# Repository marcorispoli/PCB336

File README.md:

NOTE DI DEBUG

17/04/2026

- Manca in Lista Parti L1.
 Aggiunto manualmente

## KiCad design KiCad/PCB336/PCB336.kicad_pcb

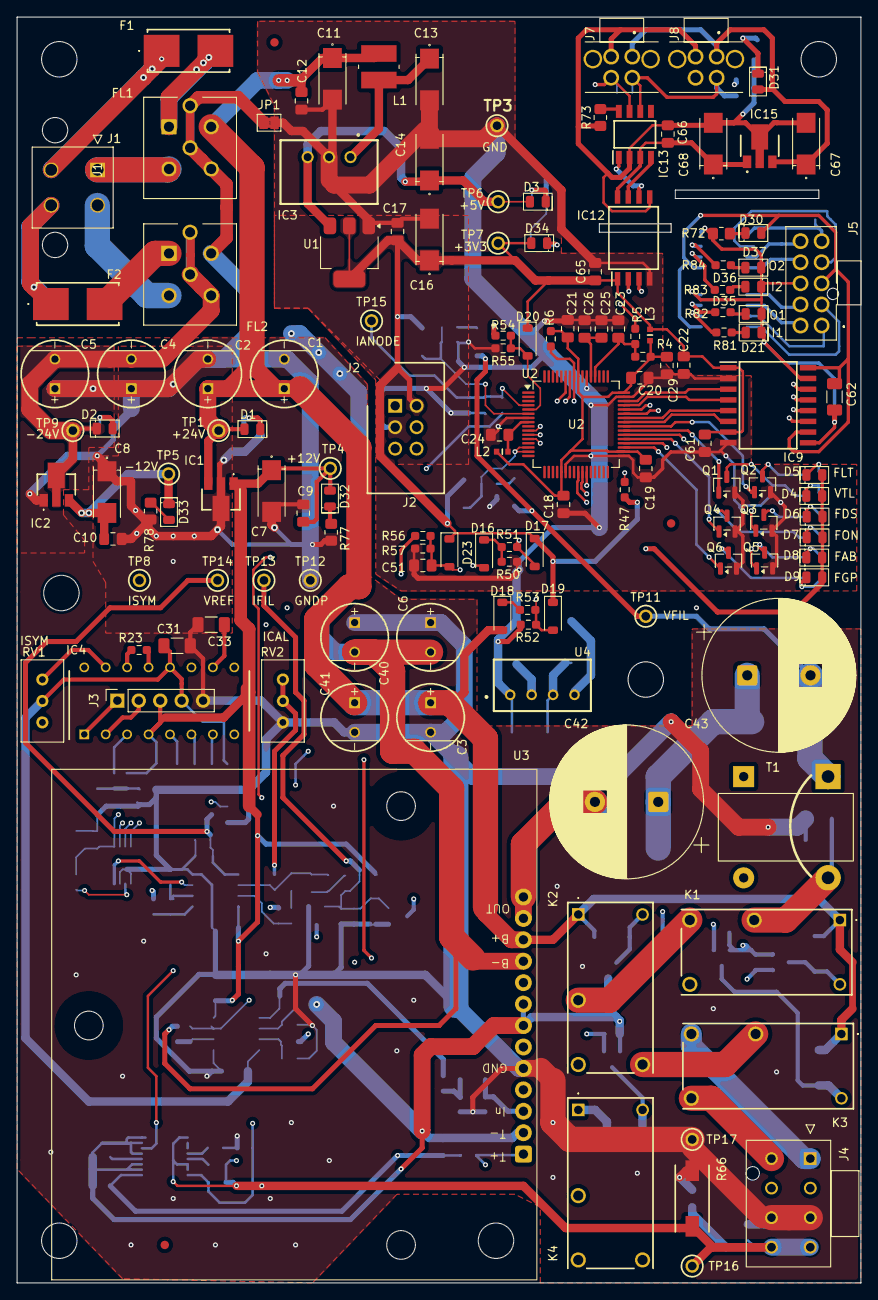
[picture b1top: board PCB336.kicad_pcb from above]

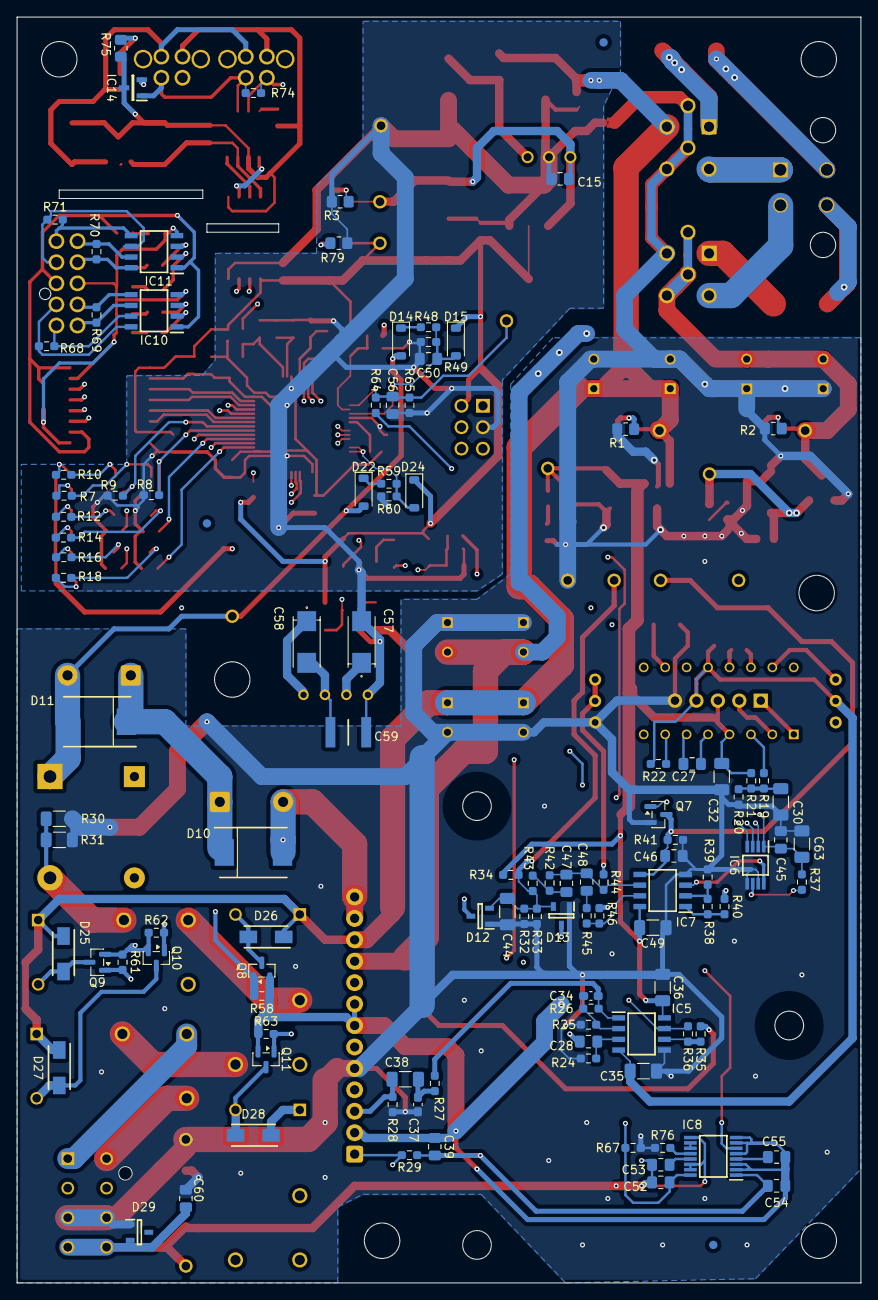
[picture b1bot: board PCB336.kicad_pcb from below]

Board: 4 copper layers, 100.0 x 150.0 mm, 250 parts (110 on the bottom side), 150 nets.

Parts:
C1, C2, C3, C4, C5, C6, C40, C41: 33uF; WCAP-HTG5_D8_H9_P3.5
C7, C8, C11, C13, C14, C16, C57, C58, C67, C68: 4.7uF; T491C
C9, C10, C12, C15, C17, C18, C19, C20, C21, C22, C23, C24, C25, C28, C39, C45, C46, C47, C50, C51, C52, C53, C54, C55, C60, C61, C65, C66: 100nF; C_0805_2012Metric_Pad1.18x1.45mm_HandSolder
C26: 4u7; C_0805_2012Metric_Pad1.18x1.45mm_HandSolder
C27, C56: 10nF; C_0805_2012Metric_Pad1.18x1.45mm_HandSolder
C29: 10uF; C_0805_2012Metric_Pad1.18x1.45mm_HandSolder
C30, C44: 10uF; C_1206_3216Metric_Pad1.33x1.80mm_HandSolder
C31, C32, C33, C35, C36, C38, C49, C62, C63: 1uF; C_1206_3216Metric_Pad1.33x1.80mm_HandSolder
C34: 100pF; C_0603_1608Metric_Pad1.08x0.95mm_HandSolder
C37: 470pF; C_0603_1608Metric_Pad1.08x0.95mm_HandSolder
C42, C43: 100uF; CP_Radial_D18.0mm_P7.50mm
C48: 47nF; C_0805_2012Metric_Pad1.18x1.45mm_HandSolder
C59: 470pF; C470pF_WURTH_APC4632X160N
D1, D2, D3, D30, D31, D32, D33, D34: GREEN; LED_0805
D4: BLUE; LED_0805
D5: RED; LED_0805
D6, D7, D8, D9, D21, D35, D36, D37: YELLOW; LED_0805
D10, D11: SK56C
D12, D13: BAT754S,215
D14, D15, D16, D17, D18, D19, D20, D22, D23, D24: 1N4148W; D_SOD-123
D25, D26, D27, D28: ES1A
D29: MMBZ6V2AL,215
F1, F2: 0154003.DRT; Littlefuse_serie_0154
FL1, FL2: BNX012-01; BNX01201
IC1: NJM78L12UA-TE1; NJM78L12UATE1
IC2: NJM79L12SU3-TE1
IC3: TSR_0.5-2450; TSR-0.5-2433
IC4: XR2206CP-F; XR2206CP
IC5: LM1458MX_NOPB; SOIC_LM1458M
IC6: MCP4821-E/MS; MCP4821_EMS
IC7: LM358BAIDR
IC8: ADUM3195BRQZ; SOP64P599X175-16N
IC9: ISO6742FDWR; ISO6742FDWR_SOIC
IC10, IC11: ADM4857ARZ-REEL7; ADM4857_SOIC
IC12: MAX22246CAWA_V+; MAX22246_SOIC127P1031X265-8N
IC13: TJA1050T_CM,118; TJA1050T_SOIC127P600X175-8N
IC14: ESD2CAN24DBZRQ1
IC15: NJM78L05UA-TE1
J1: 39-29-9043; 39-29-904Y
J2: 61200621621; uCProg_61200621621
J3: Piazzolato; PinSocket_1x05_P2.54mm_Vertical
J4: MOLEX_172298-1108; MOLEX_172298_1108
J5: 105310-2210; 1053102210
J7, J8: 105312-1104; NANOFIT_1053121104
JP1: SolderJumper_2_Bridged; SolderJumper-2_P1.3mm_Bridged2Bar_Pad1.0x1.5mm
K1, K2, K3, K4: 32.21.7.024.4000; 322170244000
L1: SRR4828A-8R2Y; SRR4828A120M
L2, L3: BLM18BD102SN1D; BLM18SP221SN1B
Q1, Q2, Q3, Q4, Q5, Q6, Q7, Q8, Q9, Q10, Q11: 2N7002LT1G; SOT-23
R1, R2, R75: 4K7; R_0805_2012Metric_Pad1.20x1.40mm_HandSolder
R3: 870R; R_0805_2012Metric_Pad1.20x1.40mm_HandSolder
R4, R24, R36, R37, R38, R39, R42, R43, R48, R51, R52, R56, R59, R67: 10K; R_0603_1608Metric_Pad0.98x0.95mm_HandSolder
R5: 330R; R_0603_1608Metric_Pad0.98x0.95mm_HandSolder
R6, R27, R64: 1K; R_0603_1608Metric_Pad0.98x0.95mm_HandSolder
R7, R10, R12, R14, R16, R18, R81, R82, R83, R84: 680R; R_0603_1608Metric_Pad0.98x0.95mm_HandSolder
R8, R9, R58, R61, R62, R63: 33K; R_0603_1608Metric_Pad0.98x0.95mm_HandSolder
R19, R20, R21, R22, R45, R54: 5K6; R_0603_1608Metric_Pad0.98x0.95mm_HandSolder
R23: 220R; R_0603_1608Metric_Pad0.98x0.95mm_HandSolder
R25, R26: 2K; R_0603_1608Metric_Pad0.98x0.95mm_HandSolder
R28: 56K; R_0603_1608Metric_Pad0.98x0.95mm_HandSolder
R29, R65: 2K2; R_0603_1608Metric_Pad0.98x0.95mm_HandSolder
R30, R31: 4K7; R_1206_3216Metric_Pad1.30x1.75mm_HandSolder
R32, R33: 200R; R_0603_1608Metric_Pad0.98x0.95mm_HandSolder
R34, R41: 27K; R_0603_1608Metric_Pad0.98x0.95mm_HandSolder
R35, R53: 87K; R_0603_1608Metric_Pad0.98x0.95mm_HandSolder
R40: 39K; R_0603_1608Metric_Pad0.98x0.95mm_HandSolder
R44, R47, R55: 4K7; R_0603_1608Metric_Pad0.98x0.95mm_HandSolder
R46: 18K; R_0603_1608Metric_Pad0.98x0.95mm_HandSolder
R49, R50, R60: 100K; R_0603_1608Metric_Pad0.98x0.95mm_HandSolder
R57: 22K; R_0603_1608Metric_Pad0.98x0.95mm_HandSolder
R66: 10R; RES_10R_SMW210R
R68, R69, R70, R71, R74: 120R; R_0603_1608Metric_Pad0.98x0.95mm_HandSolder
R72: 1K; R_0805_2012Metric_Pad1.20x1.40mm_HandSolder
R73: 33R; R_0805_2012Metric_Pad1.20x1.40mm_HandSolder
R76: 0R; R_0603_1608Metric_Pad0.98x0.95mm_HandSolder
R77, R78: 2K2; R_0805_2012Metric_Pad1.20x1.40mm_HandSolder
R79: 680R; R_0805_2012Metric_Pad1.20x1.40mm_HandSolder
RV1: 20K; Potentiometer_Bourns_3296W_Vertical
RV2: 5K; Potentiometer_Bourns_3296W_Vertical
T1: TF-108
TP1, TP4, TP5, TP6, TP7, TP9: 5000; TP_5001
TP3, TP12, TP16: 5001; TP_5001
TP8, TP11, TP13, TP14, TP15, TP17: 5002; TP_5001
U1: NCP1117ST33T3G; SOT-223-3_TabPin2
U2: ATSAME51J20A-A; TQFP-64_10x10mm_P0.5mm
U3: PCB319-2
U4: TME-0505S

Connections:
+3V3: C16.1 (+), C17.1, C22.1, C45.1, C61.1, C63.1, C65.1, D15.1 (K), D17.1 (K), D19.1 (K), D20.1 (K), D23.1 (K), D24.1 (K), D34.2 (A), IC6.1 (VDD), IC9.1 (VCC1), IC9.7 (EN1), IC12.1 (VDDA), J2.2, L3.1, R37.2, R47.2, TP7.1 (1_1), U1.2 (VO)
+5V: C14.1 (+), C15.1, C39.2, C54.1, C57.1 (+), D3.2 (A), D4.2 (A), D5.2 (A), D6.2 (A), D7.2 (A), D8.2 (A), D9.2 (A), IC3.3 (+VOUT), IC8.1 (VDD1), R29.1, TP6.1 (1_1), U1.3 (VI), U4.2 (+Vin)
+5VA: C52.1, C58.1 (+), IC8.16 (VDD2), R67.1, U4.4 (+Vout)
+5VDEV: C66.1, C68.1 (+), IC12.8 (VDDB), IC13.3 (VCC), IC15.1 (OUT)
+5V_EXT: C62.2, D30.2 (A), IC9.10 (EN2), IC9.16 (VCC2), IC10.1 (VCC), IC11.1 (VCC), J5.3
+12V: C7.1 (+), C9.1, C32.2, C36.2, C49.2, D32.2 (A), IC1.1 (OUT), IC4.4 (VCC), IC5.8 (V+), IC7.8 (V+), J3.3, R21.1, R34.1, TP4.1 (1_1)
+24V: C1.1, C2.1, C3.1, C11.1 (+), C12.1, C41.1, D1.2 (A), D18.2 (A), D25.1 (K), D26.1 (K), D27.1 (K), D28.1 (K), FL1.2 (OUTPUT), IC1.3 (IN), K1.1 (A), K2.1 (A), K3.1 (A), K4.1 (A), L1.1, TP1.1 (1_1), U3.11 (B+)
+24VDEV: C67.1 (+), D31.2 (A), IC15.3 (IN), J7.1, J8.1
-12V: C8.2 (-), C10.2, C31.2, C35.2, D33.1 (K), IC2.3 (OUT), IC4.12 (GND), IC5.4 (V-), J3.4, R22.2, RV1.2, TP5.1 (1_1)
-24V: C4.2, C5.2, C6.2, C40.2, D2.1 (K), FL2.4 (GND_OUT1), FL2.5 (GND_OUT2), FL2.6 (GND_OUT3), IC2.2 (IN), R35.2, TP9.1 (1_1), U3.10 (B-)
/CAN BUS/CANH: IC13.7 (CANH), IC14.2 (I2), J7.4, J8.4, R74.1
/CAN BUS/CANL: IC13.6 (CANL), IC14.1 (I1), J7.3, J8.3, R74.2
/ExternalSynch/EXT_IN1: IC9.12 (INC), IC10.2 (RO), R81.1
/ExternalSynch/EXT_IN1+: IC10.8 (A), J5.2, R68.1
/ExternalSynch/EXT_IN1-: IC10.7 (B), J5.1, R68.2
/ExternalSynch/EXT_IN2: IC9.11 (IND), IC11.2 (RO), R83.1
/ExternalSynch/EXT_IN2+: IC11.8 (A), J5.9, R70.1
/ExternalSynch/EXT_IN2-: IC11.7 (B), J5.10, R70.2
/ExternalSynch/EXT_OUT1: IC9.14 (OUTA), IC10.3 (DI), R82.1
/ExternalSynch/EXT_OUT1+: IC10.5 (Y), J5.7, R69.1
/ExternalSynch/EXT_OUT1-: IC10.6 (Z), J5.6, R69.2
/ExternalSynch/EXT_OUT2: IC9.13 (OUTB), IC11.3 (DI), R84.1
/ExternalSynch/EXT_OUT2+: IC11.5 (Y), J5.5, R71.1
/ExternalSynch/EXT_OUT2-: IC11.6 (Z), J5.4, R71.2
/FilamentControl/VFA: D12.3 (COM), T1.3 (O1)
/FilamentControl/VFB: D13.3 (COM), T1.4 (O2)
/FilamentControl/ffdb: IC4.1 (AMSI), J3.1, R46.2
/FilamentControl/fo: C28.1, IC4.2 (STO), J3.2, TP8.1 (1_1)
/FilamentControl/vamp: C38.2, R28.1, U3.3 (In)
/FilamentControl/vref: C46.1, IC7.5 (IN2+), Q7.3 (D), R40.1, R41.2, TP14.1 (1_1)
/Load/FILA: K2.12 (NC), K3.11 (COM)
/Load/FILA_G: J4.5, K3.12 (NC)
/Load/FILA_P: J4.1, K3.14 (NO)
/Load/FILB: K2.14 (NO), K4.11 (COM)
/Load/FILB_G: J4.6, K4.12 (NC)
/Load/FILB_P: J4.2, K4.14 (NO)
/Load/FILON: K1.14 (NO), K2.11 (COM)
/Load/VANODE: IC8.12 (VIN+), R76.2
/POWER/+B1: F1.1, J1.3
/POWER/+B2: F2.1, J1.4
/POWER/-B1: FL1.3 (GND_INPUT), J1.1
/POWER/-B2: FL2.3 (GND_INPUT), J1.2
/uController/LED_FLT: Q2.1 (G), R9.1, U2.40 (PB17)
/uController/LED_VTL: Q1.1 (G), R8.1, U2.39 (PB16)
/uController/MCLR: J2.1, R5.1
/uController/SVDIO: J2.6, U2.58 (PA31)
/uController/SVO: J2.4, U2.59 (PB30)
/uController/SWCLK: J2.5, R6.2, U2.57 (PA30)
/uController/Vuc: C18.2, C19.2, C20.1, C21.1, C29.2, L2.1, L3.2, R4.2, R6.1, U2.21 (VDDIOB), U2.34 (VDDIO), U2.48 (VDDIO), U2.56 (VDDIO)
Earth: C52.2, C53.2, C58.2 (-), C59.2, C60.2, D29.2 (CATHODE_(DIODE_2)), IC8.9 (GND2_1), IC8.14 (NC_2), IC8.15 (GND2_2), J4.4, J4.8, R66.2, TP16.1 (1_1), U4.3 (-Vout)
FILOUT: K1.11 (COM), R30.1, R31.1, T1.2
GND: C11.2 (-), C12.2, C13.2 (-), C14.2 (-), C15.2, C16.2 (-), C17.2, C18.1, C19.1, C20.2, C21.2, C22.2, C23.2, C24.1, C25.1, C26.1, C29.1, C39.1, C50.2, C51.2, C54.2, C55.2, C56.1, C57.2 (-), C59.1, C61.2, C65.2, IC3.2 (GND), IC8.2 (GND1_1), IC8.3 (NIC_1), IC8.5 (NIC_2), IC8.7 (NC_1), IC8.8 (GND1_2), IC9.2 (GND1_1), IC9.8 (GND1_2), IC12.4 (GNDA), J2.3, JP1.2 (B), Q1.2 (S), Q2.2 (S), Q3.2 (S), Q4.2 (S), Q5.2 (S), Q6.2 (S), Q8.2 (S), Q9.2 (S), Q10.2 (S), Q11.2 (S), R3.2, R8.2, R9.2, R49.1, R50.1, R52.1, R55.1, R57.1, R58.2, R60.1, R61.2, R62.2, R63.2, R65.2, R79.2, TP3.1 (1_1), U1.1 (GND), U2.7 (GNDANA), U2.22 (GND), U2.33 (GND), U2.47 (GND), U2.54 (GND), U3.2 (-T), U3.7 (n3), U3.8 (n4), U4.1 (-Vin)
GNDDEV: C66.2, C67.2 (-), C68.2 (-), IC12.5 (GNDB), IC13.2 (GND), IC14.3 (G), IC15.2 (GND_1), IC15.4 (GND_2), J7.2, J8.2, R73.1, R75.2
GNDPWR: C1.2, C2.2, C3.2, C4.1, C5.1, C6.1, C7.2 (-), C8.1 (+), C9.2, C10.1, C30.1, C31.1, C32.1, C33.1, C35.1, C36.1, C37.1, C40.1, C41.2, C44.1, C45.2, C46.2, C49.1, C60.1, C63.2, D12.1 (A), D13.1 (A), D29.1 (CATHODE_(DIODE_1)), FL1.4 (GND_OUT1), FL1.5 (GND_OUT2), FL1.6 (GND_OUT3), FL2.2 (OUTPUT), IC1.2 (GND), IC2.1 (GND), IC5.5 (+B), IC6.5 (~LDAC), IC6.7 (VSS), IC7.4 (V-), J3.5, J4.3, J4.7, JP1.1 (A), Q7.2 (S), R1.2, R2.2, R20.2, R24.2, R25.2, R28.2, R30.2, R31.2, R32.2, R33.2, R39.1, R41.1, R66.1, R67.2, R76.1, R77.2, R78.2, RV2.3, TP12.1 (1_1), TP17.1 (1_1), U3.5 (GNDP)
GND_EXT: C62.1, D21.1 (K), D35.1 (K), D36.1 (K), D37.1 (K), IC9.9 (GND2_1), IC9.15 (GND2_2), IC10.4 (GND), IC11.4 (GND), J5.8, R72.2
MONITOR_24VNEG: D16.2 (A), IC5.7 (OB), R36.1
MONITOR_IFIL: C44.2, D12.2 (K), D13.2 (K), R32.1, R33.1, R34.2, R43.1, R54.2, TP13.1 (1_1)
MONITOR_TAMP: R29.2, R56.2, U3.1 (+T)
unnamed: C13.1 (+), IC3.1 (+VIN), L1.2
unnamed: C30.2, R19.2, R20.1, R21.2
unnamed: C37.2, C38.1, R27.2
unnamed: C47.2, R42.1, R43.2
unnamed: C48.1, R45.1
unnamed: D1.1 (K), R1.1
unnamed: D2.2 (A), R2.1
unnamed: D3.1 (K), R3.1
unnamed: D4.1 (K), R7.1
unnamed: D5.1 (K), R10.1
unnamed: D6.1 (K), R12.1
unnamed: D7.1 (K), R14.1
unnamed: D8.1 (K), R16.1
unnamed: D9.1 (K), R18.1
unnamed: C42.2, D10.2 (A), U3.12 (Out), U3.13 (Out2)
unnamed: C42.1, C43.1, D10.1 (K), D11.1 (K)
unnamed: D14.1 (K), R48.2
unnamed: D16.1 (K), R50.2, R51.2
unnamed: D18.1 (K), R53.2
unnamed: D21.2 (A), R81.2
unnamed: D22.1 (K), R59.2
unnamed: D25.2 (A), K1.2 (B), Q9.3 (D)
unnamed: D26.2 (A), K2.2 (B), Q8.3 (D)
unnamed: D27.2 (A), K3.2 (B), Q10.3 (D)
unnamed: D28.2 (A), K4.2 (B), Q11.3 (D)
unnamed: D30.1 (K), R72.1
unnamed: D31.1 (K), R75.1
unnamed: D32.1 (K), R77.1
unnamed: D33.2 (A), R78.1
unnamed: D34.1 (K), R79.1
unnamed: D35.2 (A), R82.2
unnamed: D36.2 (A), R83.2
unnamed: D37.2 (A), R84.2
unnamed: F1.2, FL1.1 (INPUT)
unnamed: F2.2, FL2.1 (INPUT)
unnamed: C33.2, IC4.10 (BIAS)
unnamed: IC4.3 (MO), R19.1
unnamed: IC4.15 (SYMA1), RV1.1
unnamed: IC4.16 (SYMA2), RV1.3
unnamed: C27.1, IC4.5 (TC1)
unnamed: C27.2, IC4.6 (TC2)
unnamed: IC4.7 (TR1), R22.1
unnamed: IC4.13 (WAVEA1), R23.2
unnamed: IC4.14 (WAVEA2), R23.1
unnamed: C28.2, IC5.3 (+A), R24.1
unnamed: C34.1, IC5.2 (-A), R25.1, R26.2
unnamed: IC5.6 (-B), R35.1, R36.2
unnamed: C34.2, IC5.1 (OA), R26.1, R27.1
unnamed: IC6.8 (VOUT), IC7.3 (IN1+)
unnamed: IC6.6 (~SHDN), R37.1
unnamed: IC7.2 (IN1-), R38.2, R39.2
unnamed: C47.1, C48.2, IC7.6 (IN2-), R42.2, R44.2
unnamed: IC7.1 (OUT1), R38.1, R40.2
unnamed: IC7.7 (OUT2), R45.2, R46.1
unnamed: IC8.10 (VOUT2), IC8.11 (VIN-)
unnamed: IC8.6 (VOUT1), R64.1
unnamed: C55.1, IC8.4 (VREF1)
unnamed: C53.1, IC8.13 (VREF2)
unnamed: IC12.7 (IN1), IC13.4 (RXD)
unnamed: IC12.6 (OUT2), IC13.1 (TXD)
unnamed: IC13.8 (S), R73.2
unnamed: Q1.3 (D), R7.2
unnamed: Q2.3 (D), R10.2
unnamed: Q3.3 (D), R12.2
unnamed: Q4.3 (D), R14.2
unnamed: Q5.3 (D), R16.2
unnamed: Q6.3 (D), R18.2
unnamed: R44.1, RV2.1, RV2.2
unnamed: C24.2, L2.2, U2.8 (VDDANA)
unnamed: C25.2, C26.2, U2.53 (VDDCORE)
unnamed: C23.1, R4.1, R5.2, U2.52 (~RESET)
V_FILOUT: C43.2, D11.2 (A), D14.2 (A), D22.2 (A), T1.1, TP11.1 (1_1)
uC_24VNEG_ANL: D17.2 (A), R51.1, U2.11 (PB08)
uC_24V_ANL: D19.2 (A), R52.2, R53.1, U2.10 (PB07)
uC_CAN_RX0: IC12.2 (OUT1), U2.44 (PA23)
uC_CAN_TX0: IC12.3 (IN2), U2.43 (PA22)
uC_CLK: IC6.3 (SCK), U2.26 (PB13)
uC_CS: IC6.2 (~CS), U2.27 (PB14)
uC_EXT_IN1: IC9.5 (OUTC), U2.42 (PA21)
uC_EXT_IN2: IC9.6 (OUTD), U2.41 (PA20)
uC_EXT_OUT1: IC9.3 (INA), U2.46 (PA25)
uC_EXT_OUT2: IC9.4 (INB), U2.45 (PA24)
uC_FILON: Q4.1 (G), Q9.1 (G), R61.1, U2.37 (PA18)
uC_FOCUS_BA: Q5.1 (G), Q8.1 (G), R58.1, U2.36 (PA17)
uC_FOCUS_PG: Q6.1 (G), Q10.1 (G), Q11.1 (G), R62.1, R63.1, U2.35 (PA16)
uC_IANODE_ANL: C56.2, R64.2, R65.1, TP15.1 (1_1), U2.4 (PA03)
uC_IFIL_ANL: D20.2 (A), R54.1, R55.2, U2.5 (PB04)
uC_IFREQ_ANL: D24.2 (A), R59.1, R60.2, U2.14 (PA05), U2.15 (PA06)
uC_REFDIS: Q3.1 (G), Q7.1 (G), R47.1, U2.38 (PA19)
uC_SDO: IC6.4 (SDI), U2.25 (PB12)
uC_TAMP_ANL: C51.1, D23.2 (A), R56.1, R57.2, U2.12 (PB09)
uC_VFIL_ANL: C50.1, D15.2 (A), R48.1, R49.2, U2.6 (PB05)

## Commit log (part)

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2026-01-29 Creazione Progetto
2026-01-29 Aggiornato schema boost
2026-02-11 Aggiornato Boost e aggiunto relè filamenti
2026-02-13 Completato Boost e Load
2026-02-13 Completato Schematico Manca da completare la revisione della lista parti
2026-02-17 Aggiunto Filtro Ingresso e predisposizione SIL per tensione di griglia
2026-02-19 Modificato schematico su richiesta Osvaldina
2026-02-23 RELEASE-0
2026-02-23 Formattata la lista parti
2026-04-17 Modificato Lista parti: mancava L1
